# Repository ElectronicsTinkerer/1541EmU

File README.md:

# 1541EmU
Source code and eagle files for the 1541 Emulator

***Note:** This repository has now been archived on 2026-04-12, as I no longer have any plans on continuing development (and besides, there's some waaay better emulators on the market now 🙂). I will keep the repo up since I think it makes for an interesting, minimal-ish implementation of the IEC protocol, and maybe there's a few people who might find it useful.*

<hr>

 _Description_
 
  The 1541EmU is a 1541 emulator for the c64. It is based on the ATMEGA328P-PU and interfaces over the IEC bus. Files are stored on a micro SD card formatted to FAT32 using the 8.3 file name format. Included is a drive reset button that resets the drive, but not the computer. There is also a solder jumper to enable reset-by-computer, which allows the c64's reset line to reset the drive.
 <br> 
 I have a demo <a href="https://youtu.be/4uivsbCX4fI">here</a>. (https://youtu.be/4uivsbCX4fI)
  
 _Features_
 
  * Save and load files with almost any filename (ASCII Characters only)
  * Change file order on disk (Through a computer)
  * <code>LOAD "*",8</code> is allowed
  * View directory
  * Overwrite existing files on disk
  * Auto initialization of filename translation file (DIR)
  * Cassette interface pass through connector.
  * ICSP and Tx/Rx headers
  * Power and status LEDs
  * Compatible with the Arduino IDE

# Board
Latest board revision: 1.1 on September 9, 2018
  (Note: there is no official revision 1.0)
  
  1) Checked schematic, part numbers, and part footprint sizing.
  2) Fixed board dimension issue
  
# Source
Latest revision: EFS1.00 (Extended File System v1.00) on October 23, 2018
  
  1) Added the "DIR" file that translates the expected filename from the c64 to the actual name that is stored on the SD
  2) Fixed "DEVICE NOT PRESENT ERROR" (as far as I can test the drive)

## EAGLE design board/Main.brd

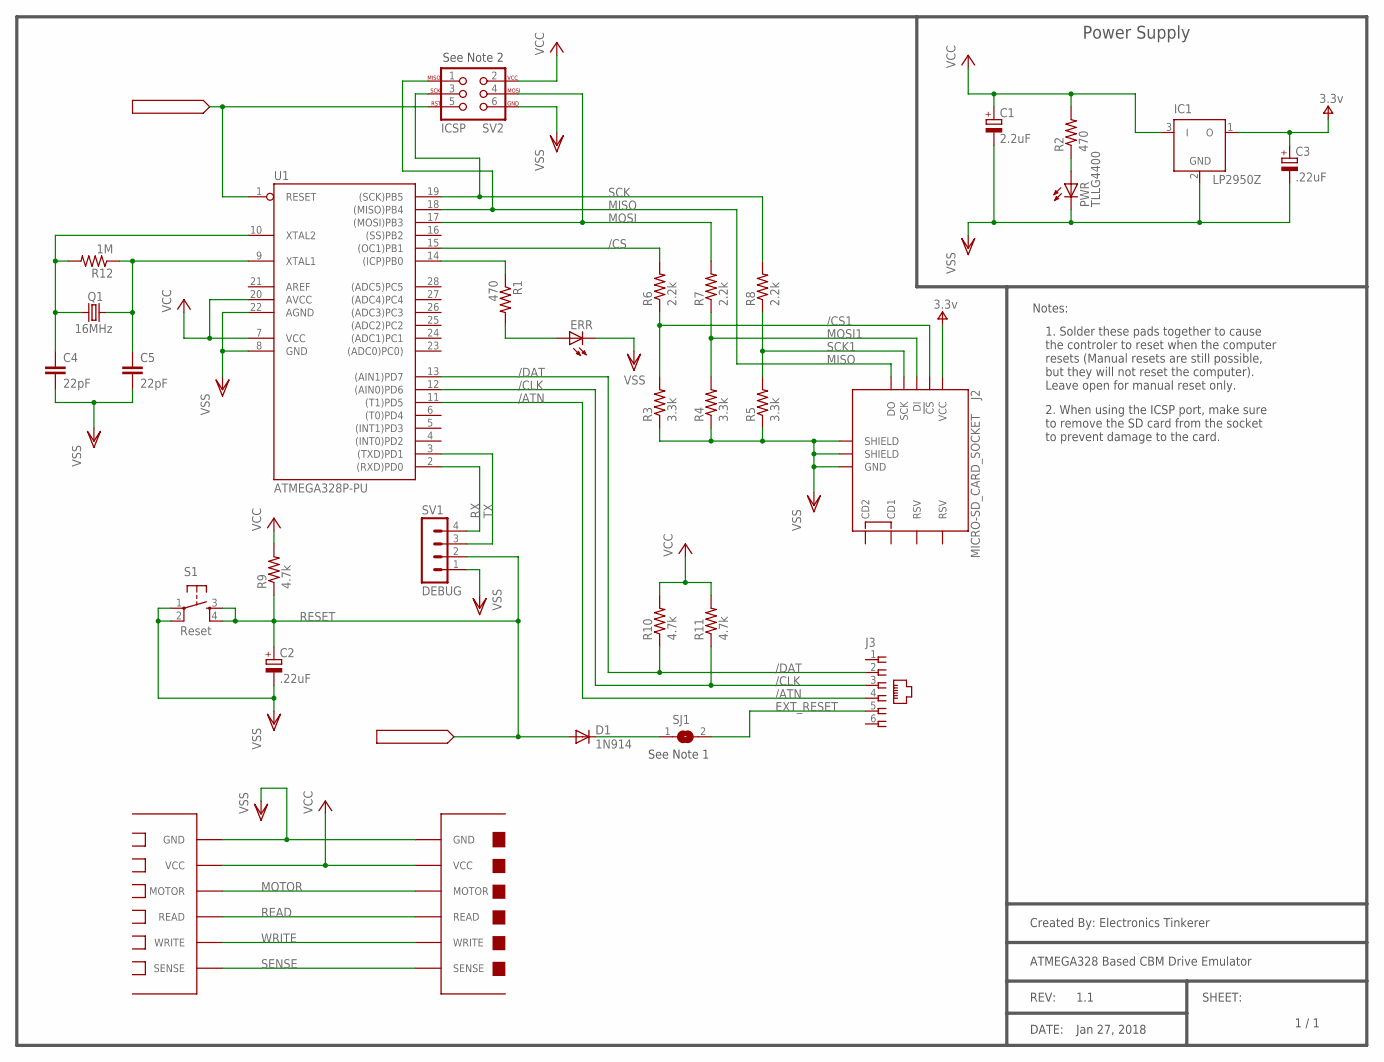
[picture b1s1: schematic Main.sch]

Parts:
C1: 2.2uF; E2-5
C2, C3: .22uF; E1,5-4
C4, C5: 22pF; C050-024X044
D1: 1N914; DO41-5
ERR: TLLR4400; LED3MM
IC1: LP2950Z; TO92
J2: MICRO-SD_CARD_SOCKET; MICRO-SD-SOCKET
J3: 520470-3
PWR: TLLG4400; LED3MM
Q1: 16MHz; HC49/S
R1, R2: 470; 0204/5
R3, R4, R5: 3.3k; 0204/5
R6, R7, R8: 2.2k; 0204/5
R9, R10, R11: 4.7k; 0204/5
R12: 1M; 0204/5
S1: DTS-6
SJ1: SJ
SV1: DEBUG; MA04-1
SV2: AVR_SPI_PROG; 2X3
U1: ATMEGA328P-PU; DIL28-3
U$1: CASSETT-BOARDCEC-6; SOLDER-PADS_3,96-M
U$2: CASSETT-CON; SOLDER-PADS_3,96-F

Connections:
/ATN: J3.4, U1.11 ((T1)PD5)
/CLK: J3.3, R11.1, U1.12 ((AIN0)PD6)
/CS: R6.2, U1.15 ((OC1)PB1)
/CS1: J2.CS (!CS), R3.2, R6.1
/DAT: J3.2, R10.1, U1.13 ((AIN1)PD7)
EXT_RESET: J3.5, SJ1.2
MISO: J2.DO, SV2.1, U1.18 ((MISO)PB4)
MOSI: R7.2, SV2.4, U1.17 ((MOSI)PB3)
MOSI1: J2.DI, R4.2, R7.1
MOTOR: U$1.MOTOR, U$2.MOTOR
unnamed: R1.1, U1.14 ((ICP)PB0)
unnamed: PWR.A, R2.1
unnamed: ERR.A, R1.2
unnamed: D1.C, SJ1.1
unnamed: C4.1, Q1.1, R12.2, U1.10 (XTAL2)
unnamed: C5.1, Q1.2, R12.1, U1.9 (XTAL1)
READ: U$1.READ, U$2.READ
RESET: C2.+, D1.A, R9.1, S1.3, S1.4, SV1.2, SV2.5, U1.1 (RESET)
RX: SV1.4, U1.2 ((RXD)PD0)
SCK: R8.2, SV2.3, U1.19 ((SCK)PB5)
SCK1: J2.SCLK (SCK), R5.2, R8.1
SENSE: U$1.SENSE, U$2.SENSE
TX: SV1.3, U1.3 ((TXD)PD1)
V+: C3.+, IC1.1 (O), J2.VCC
VCC: C1.+, IC1.3 (I), R2.2, R9.2, R10.2, R11.2, SV2.2, U1.7 (VCC), U1.20 (AVCC), U$1.VCC, U$2.VCC
VSS: C1.-, C2.-, C3.-, C4.2, C5.2, ERR.K (C), IC1.2 (GND), J2.GND, J2.GND1 (SHIELD), J2.GND3 (SHIELD), PWR.K (C), R3.1, R4.1, R5.1, S1.1, S1.2, SV1.1, SV2.6, U1.8 (GND), U1.22 (AGND), U$1.GND, U$2.GND
WRITE: U$1.WRITE, U$2.WRITE

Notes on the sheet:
Power Supply
See Note 1
1. Solder these pads together to cause the controler to reset when the computer resets (Manual resets are still possible, but they will not reset the computer). Leave open for manual reset only.
Notes:
Created By: Electronics Tinkerer
ATMEGA328 Based CBM Drive Emulator
REV:
1.1
DATE:
Jan 27, 2018
SHEET:
1 / 1
2. When using the ICSP port, make sure to remove the SD card from the socket to prevent damage to the card.
See Note 2

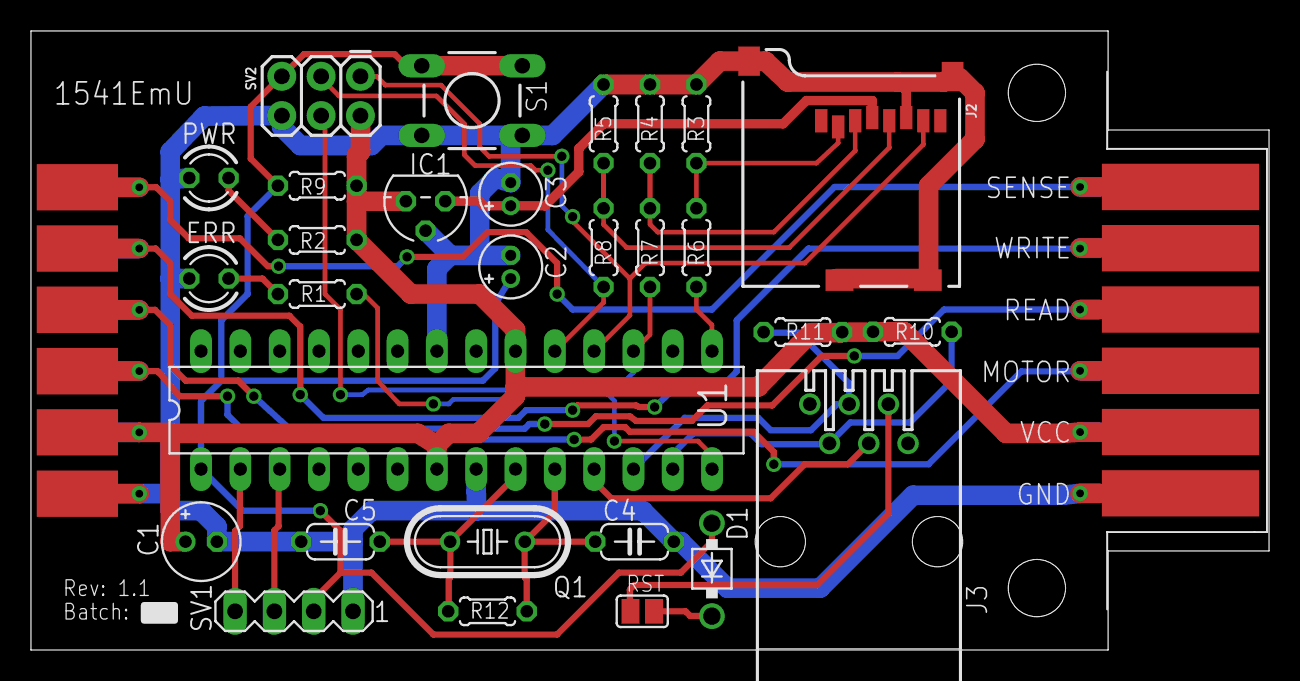
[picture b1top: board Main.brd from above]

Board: 2 copper layers, 80.0 x 40.0 mm, 31 parts (0 on the bottom side), 27 nets.

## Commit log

2018-11-05 Upload all files
2018-11-06 Update Note 1 in schematic
2026-04-12 Update README with archival notice
    Added note about repository archival and development status.

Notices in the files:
parts and their libraries:
SparkFun-Connectors: Licensing: Creative Commons ShareAlike 4.0 International - https://creativecommons.org/licenses/by-sa/4.0
